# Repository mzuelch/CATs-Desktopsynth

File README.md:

<h1>CATs-DesktopSynths</h1>
<p>This is my repository for my desktop synths or supplementa for 3rd party synths. Files given via the "Gerber" directories are actual production data used for my own prototyping. Bugs are to be expected. Corrections for finished boards marked as "working" are done in KiCAD only.</p>
<p>Please read the "Known Issues" section given in this repository as "ReadMe.md" whenever appropriate.</p>
<h1>License</h1>
<p>Code (AVR projects): GPL3.0.</p>
<p>Code (STM32F projects): MIT license.</p>
<p>Hardware: cc-by-sa-3.0</p>
<p>unless otherwise specified</p>
<h2>Projects</h2>
<h3><a href="https://github.com/mzuelch/CATs-Desktopsynth/tree/main/Projects/Minidexed">MiniClumsyDexed</a></h3>

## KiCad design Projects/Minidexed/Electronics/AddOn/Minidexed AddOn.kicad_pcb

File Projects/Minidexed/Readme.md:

<h1>MiniClumsyDexed</h1>
<p>Addon board and Case for:</p>
<p><a href="https://github.com/probonopd/MiniDexed">MiniDexed by probonopd</a></p>
<p><a href="https://github.com/gmcn42/clumsyMIDI">clumsyMIDI by gmcn42</a></p>
<h2><a href="./Mechanics/Assembly/Readme.md">Assembly Instructions</a></h2>

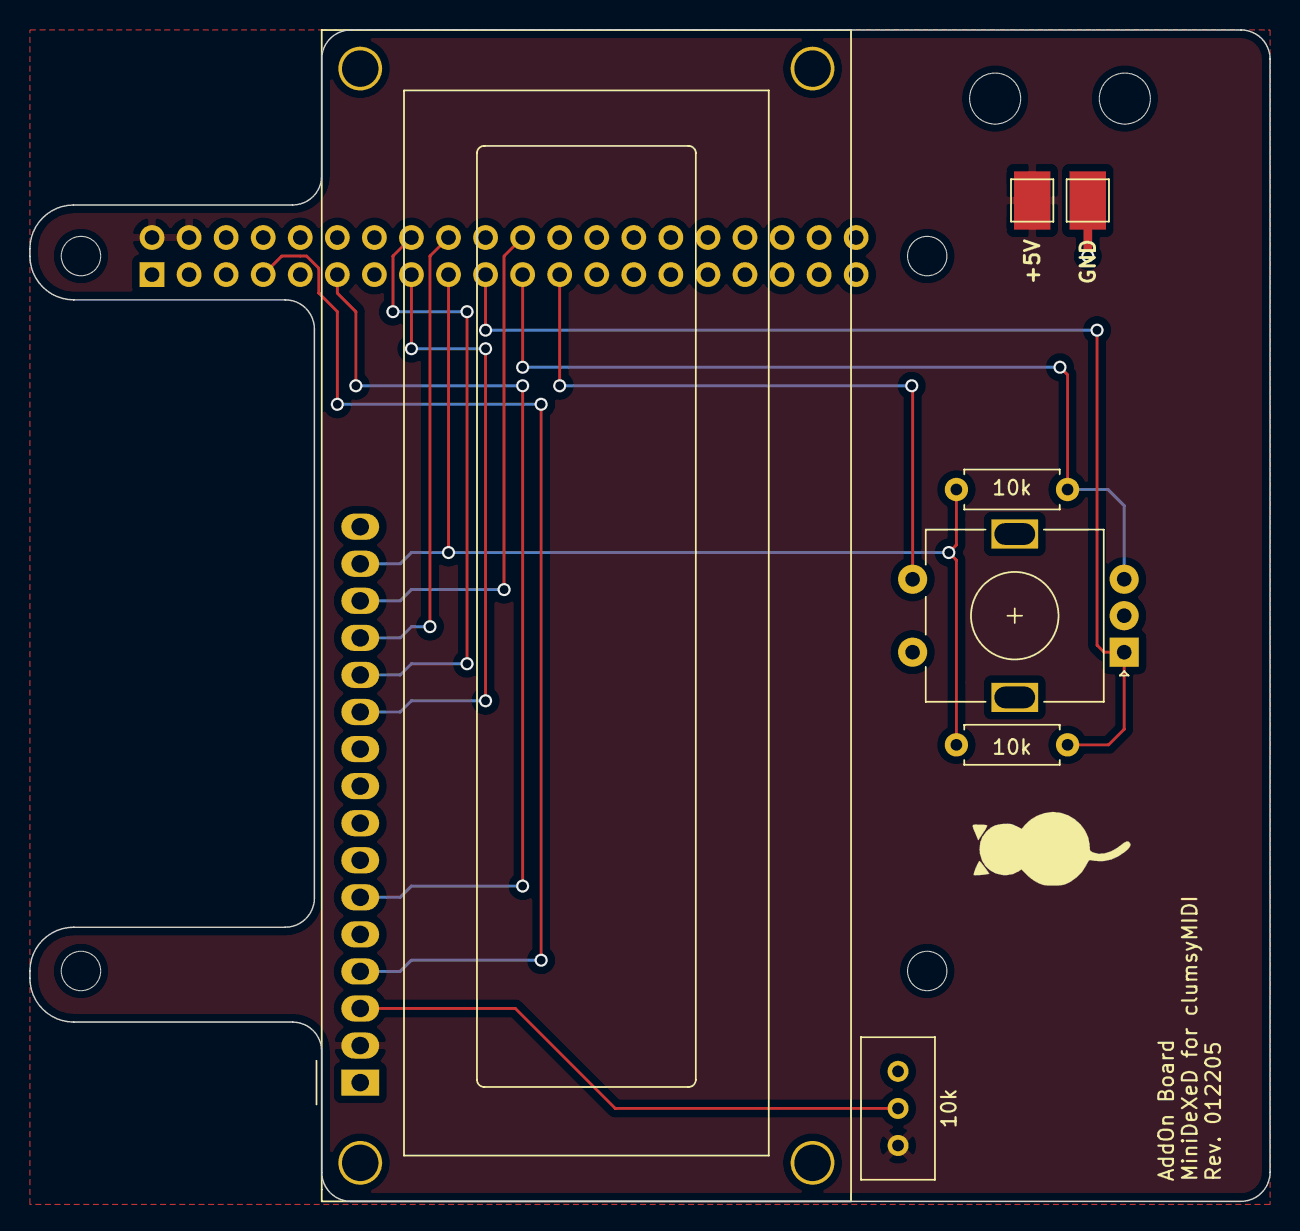
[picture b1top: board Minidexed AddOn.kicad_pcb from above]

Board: 2 copper layers, 85.0 x 80.3 mm, 14 parts (1 on the bottom side), 13 nets.

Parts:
DS1: WC1602A
H1, H2: MountingHole; MountingHole_3.5mm
MK1, MK2, MK3, MK4: M2.5; MountingHole_2.7mm_M2.5
P1: GPIO; PinSocket_2x20_P2.54mm_Vertical
R1, R2: 10k; R_Axial_DIN0207_L6.3mm_D2.5mm_P7.62mm_Horizontal
RV1: 10k; Potentiometer_Bourns_3296W_Vertical
SW1: Encoder; RotaryEncoder_Alps_EC11E-Switch_Vertical_H20mm
TP1: +5V; TestPoint_Pad_2.5x2.5mm
TP2: GND; TestPoint_Pad_2.5x2.5mm

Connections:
+3V3: DS1.15, P1.17, R1.1, R2.1
+5V: DS1.2, P1.2, P1.4, RV1.1, TP1.1
/GPIO4(GCLK): DS1.4, P1.7
/GPIO9(SPI0_MISO): P1.21, R1.2, SW1.B
/GPIO10(SPI0_MOSI): P1.19, R2.2, SW1.A
/GPIO11(SPI0_SCK): P1.23, SW1.S1
/GPIO17(GEN0): DS1.6, P1.11
/GPIO22(GEN3): DS1.11, P1.15
/GPIO23(GEN4): DS1.12, P1.16
/GPIO24(GEN5): DS1.13, P1.18
/GPIO25(GEN6): DS1.14, P1.22
GND: DS1.1, DS1.5, DS1.16, P1.6, P1.14, P1.20, P1.25, P1.30, P1.34, P1.39, RV1.3, SW1.C, SW1.S2, TP2.1
unnamed: DS1.3, RV1.2

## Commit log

2022-06-01 Minidexed Mechanical
2022-06-01 Minidexed Gerber
2022-06-03 Minidexed
2022-06-04 Correction Case
2022-06-05 3D MiniDexed
2022-06-06 Minidexed Assembly
2022-06-06 Assembly
